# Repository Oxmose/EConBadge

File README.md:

# EConBadge
E-Ink Convention Badge | Connected badge to display your favorite images and texts at conventions.

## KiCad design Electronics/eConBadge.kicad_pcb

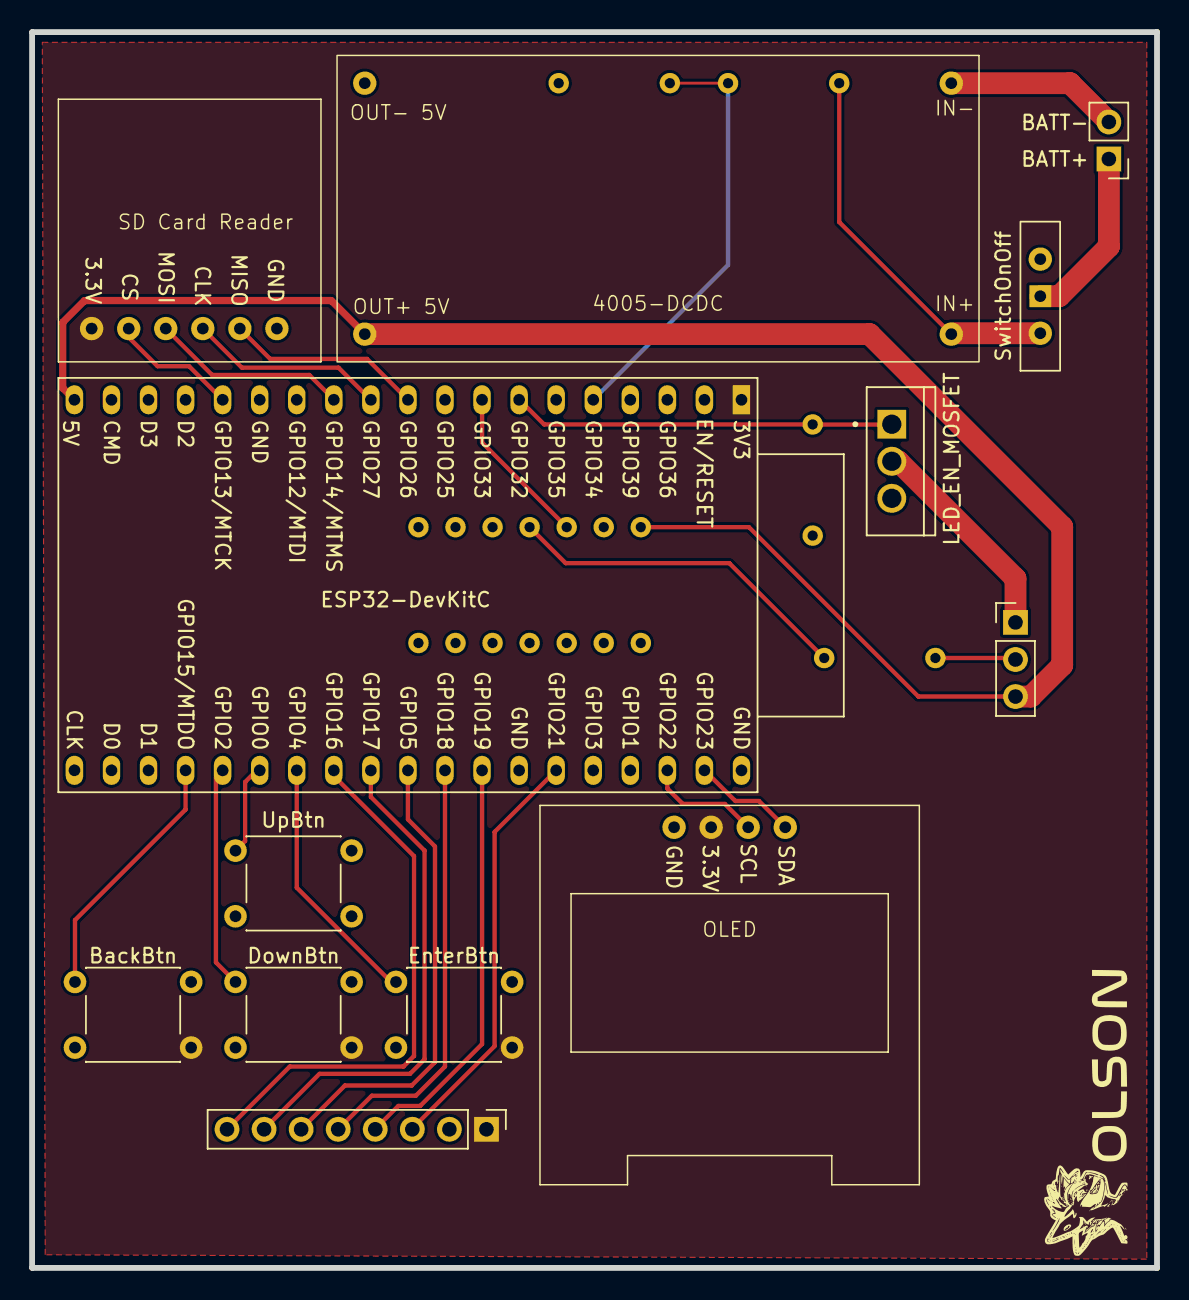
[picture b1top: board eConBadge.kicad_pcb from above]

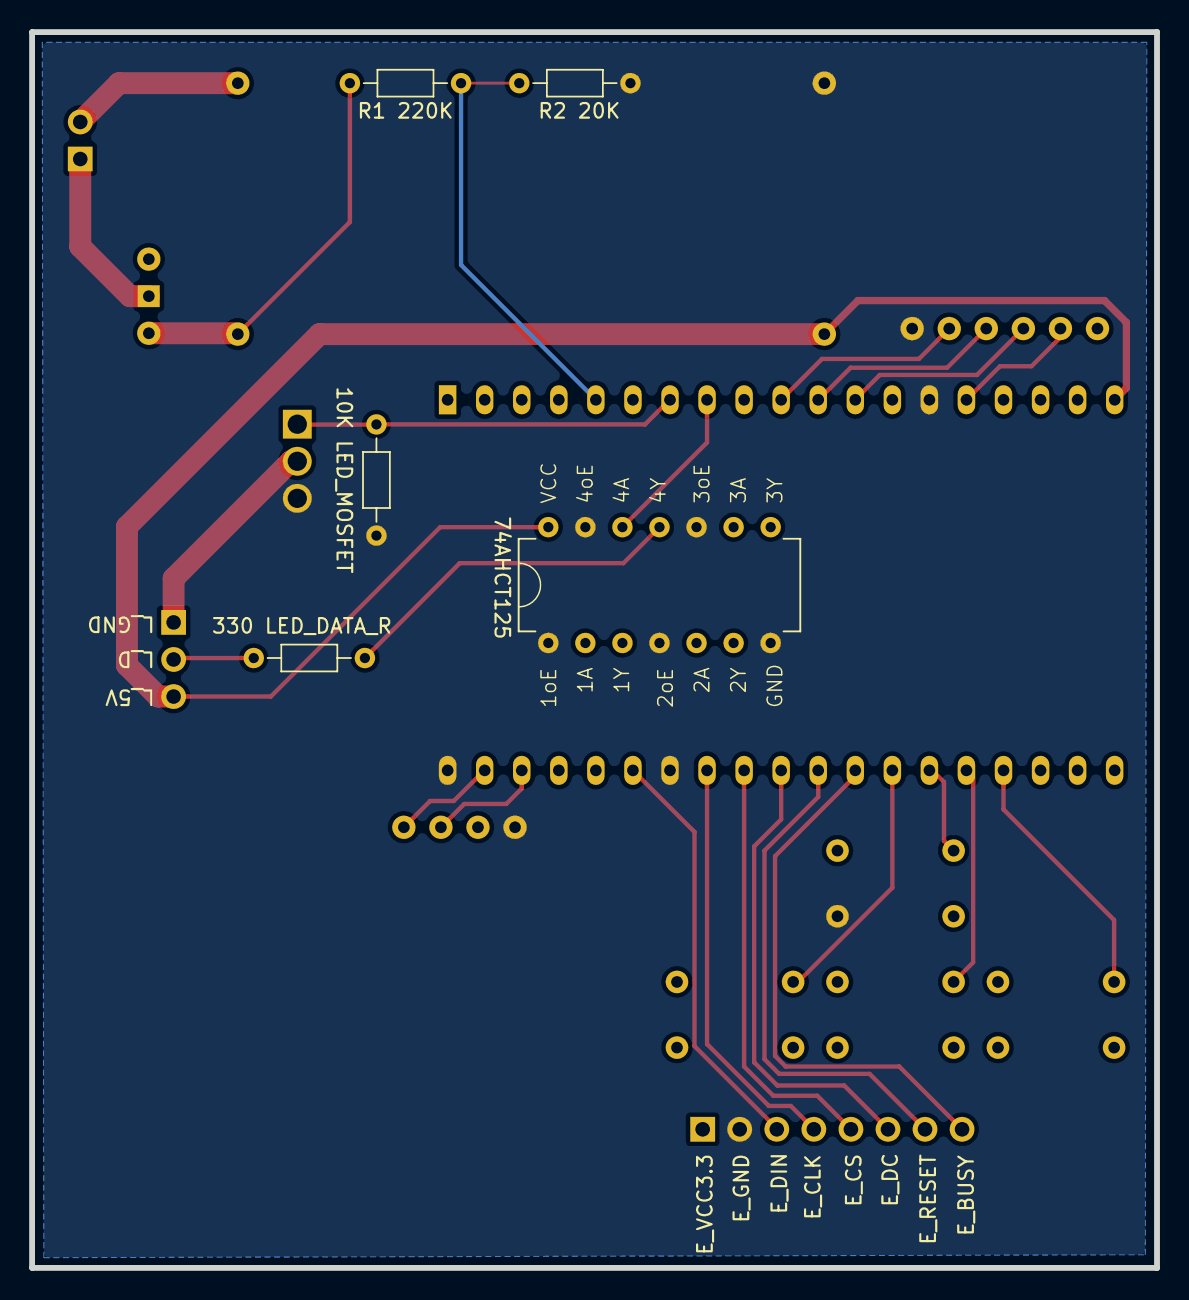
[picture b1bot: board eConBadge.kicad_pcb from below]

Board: 2 copper layers, 77.1 x 84.7 mm, 18 parts (5 on the bottom side), 28 nets.

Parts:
10K LED_MOSFET, 330 LED_DATA_R: R_Axial_DIN0204_L3.6mm_D1.6mm_P7.62mm_Horizontal
74AHCT125 : 74AHCT125; DIP794W45P254L1930H508Q14
4005-DCDC: DC-DC Regulator; 4005DCDC
BATT-: PinHeader_1x02_P2.54mm_Vertical
BackBtn: Button
DownBtn: Button
EInkConnector: PinHeader_1x08_P2.54mm_Vertical
ESP32: ESP32-DevKitC
EnterBtn: Button
LEDConnector: PinHeader_1x03_P2.54mm_Vertical
LED_EN_MOSFET: TRANS_RFP30N06LE
OLED: SSD1306_0.96_OLED
R1 220K: R_Axial_DIN0204_L3.6mm_D1.6mm_P7.62mm_Horizontal
R2 20K: R2 20K; R_Axial_DIN0204_L3.6mm_D1.6mm_P7.62mm_Horizontal
SDCardReader: 10k; SDCardReader
SwitchOnOff: SW_Slide-03_Wuerth-WS-SLTV_10x2.5x6.4_P2.54mm
UpBtn: Button

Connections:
BATT_IN_GND: 4005-DCDC.4, BATT-.2
BATT_IN_REG: 4005-DCDC.3, R1 220K.1, SwitchOnOff.2
BATT_IN_VCC: BATT-.1, SwitchOnOff.1
BATT_V_MEASURE: ESP32.5, R1 220K.2, R2 20K.1
BTN_BACK: BackBtn.1, ESP32.23
BTN_DOWN: DownBtn.1, ESP32.24
BTN_ENTER: ESP32.26, EnterBtn.1
BTN_UP: ESP32.25, UpBtn.1
EINK_BUSY: EInkConnector.8, ESP32.27
EINK_CLK: EInkConnector.4, ESP32.31
EINK_CS: EInkConnector.5, ESP32.30
EINK_DC: EInkConnector.6, ESP32.29
EINK_DIN: EInkConnector.3, ESP32.33
EINK_RESET: EInkConnector.7, ESP32.28
GND: 10K LED_MOSFET.1, 74AHCT125.1, 74AHCT125.4, 74AHCT125.7, 74AHCT125.10, 74AHCT125.13, 4005-DCDC.2, EInkConnector.2, ESP32.14, ESP32.32, ESP32.38, LED_EN_MOSFET.3, OLED.1, R2 20K.2, SDCardReader.6, UpBtn.2
LED_DATA_3V: 74AHCT125.12, ESP32.8
LED_DATA_5V_OUT: 330 LED_DATA_R.1, LEDConnector.2
LED_DATA_5V_SHIFT: 74AHCT125.11, 330 LED_DATA_R.2
LED_EN: 10K LED_MOSFET.2, ESP32.7, LED_EN_MOSFET.1
LED_GND: LEDConnector.1, LED_EN_MOSFET.2
OLED_CLK: ESP32.36, OLED.3
OLED_SDA: ESP32.37, OLED.4
SD_CLK: ESP32.11, SDCardReader.4
SD_CS: ESP32.15, SDCardReader.2
SD_MISO: ESP32.10, SDCardReader.5
SD_MOSI: ESP32.12, SDCardReader.3
VCC3.3: BackBtn.2, DownBtn.2, EInkConnector.1, ESP32.1, EnterBtn.2, OLED.2, SDCardReader.1
VCC_5V: 74AHCT125.14, 4005-DCDC.1, ESP32.19, LEDConnector.3

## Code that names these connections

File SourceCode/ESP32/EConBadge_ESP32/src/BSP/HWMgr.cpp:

/*******************************************************************************
 * @file HWMgr.cpp
 *
 * @author Alexy Torres Aurora Dugo
 *
 * @date 30/03/2021
 *
 * @version 1.0
 *
 * @brief This file defines the hardware layer.
 *
 * @details This file defines the hardware layer. This layer provides services
 * to interact with the ESP32 module hardware.
 *
 * @copyright Alexy Torres Aurora Dugo
 ******************************************************************************/


/*******************************************************************************
 * INCLUDES
 ******************************************************************************/
#include <string>      /* std::string*/
#include <Types.h>     /* Defined Types */
#include <Logger.h>    /* Logging service */
#include <esp_mac.h>   /* Mac address provider */
#include <esp_timer.h> /* Timer provider */

/* Header File */
#include <HWMgr.h>

/*******************************************************************************
 * CONSTANTS
 ******************************************************************************/
/* None */

/*******************************************************************************
 * MACROS
 ******************************************************************************/

/* None */

/*******************************************************************************
 * STRUCTURES AND TYPES
 ******************************************************************************/

/* None */

/*******************************************************************************
 * GLOBAL VARIABLES
 ******************************************************************************/

/************************* Imported global variables **************************/
/* None */

/************************* Exported global variables **************************/
/** @brief See HWManage.h */
std::string HWManager::HWUID_;
/** @brief See HWManage.h */
std::string HWManager::MACADDR_;
/** @brief See HWManage.h */
uint64_t HWManager::TIME_;

/** @brief Generic SPI bus */
SPIClass GEN_SPI(HSPI);

/************************** Static global variables ***************************/
/** @brief Decimal to Hexadecimal convertion table */
static const char spkHexTable[16] = {
    '0', '1', '2', '3', '4', '5', '6', '7',
    '8', '9', 'A', 'B', 'C', 'D', 'E', 'F'
};

/*******************************************************************************
 * STATIC FUNCTIONS DECLARATIONS
 ******************************************************************************/

/* None */

/*******************************************************************************
 * FUNCTIONS
 ******************************************************************************/

/* None */

/*******************************************************************************
 * CLASS METHODS
 ******************************************************************************/

const char* HWManager::GetHWUID(void)
{
    uint8_t value[6];
    uint8_t i;

    /* Check if the HWUID was already generated */
    if(HWUID_.size() == 0)
    {
        HWUID_ = "ECB-";

        esp_read_mac(value, ESP_MAC_BT);

        for(i = 0; i < 4; ++i)
        {
            HWUID_ += std::string(1, spkHexTable[(value[i] >> 4) & 0xF]) +
                      std::string(1, spkHexTable[value[i] & 0xF]);
        }
    }

    /* Copy HWUID */
    return HWUID_.c_str();
}

const char* HWManager::GetMacAddress(void)
{
    uint8_t i;
    uint8_t value[6];

    /* Check if the HWUID was already generated */
    if(MACADDR_.size() == 0)
    {
        esp_read_mac(value, ESP_MAC_BT);

        MACADDR_ = "";
        for(i = 0; i < 6; ++i)
        {
            MACADDR_ += std::string(1, spkHexTable[(value[i] >> 4) & 0xF]) +
                        std::string(1, spkHexTable[value[i] & 0xF]);
            if(i < 5)
            {
                MACADDR_ += ":";
            }
        }
    }

    /* Copy HWUID */
    return MACADDR_.c_str();
}

uint64_t HWManager::GetTime(void)
{
    TIME_ = (uint64_t)esp_timer_get_time();

    return TIME_;
}

void HWManager::Init(void)
{
    /* Begin ELINK and General SPI (with custom pins) */
    EINK_SPI.begin(GPIO_EINK_CLK, 33, GPIO_EINK_DIN, GPIO_EINK_CS);
    GENERAL_SPI.begin(GPIO_SD_CLK, GPIO_SD_MISO, GPIO_SD_MOSI, GPIO_SD_CS);

    /* Init time */
    TIME_ = 0;
}

void HWManager::DelayExecUs(const uint64_t kDelayUs)
{
    uint64_t passiveTime;
    uint64_t activeTime;
    uint64_t startTime;

    startTime = (uint64_t)esp_timer_get_time();

    /* Calculate how much we can spend in passive wait */
    passiveTime = kDelayUs / 1000 / portTICK_PERIOD_MS;

    /* Check if we can use a precise wait */
    if(passiveTime != 0)
    {
        vTaskDelay(passiveTime);
    }

    activeTime = (uint64_t)esp_timer_get_time() - startTime;

    /* Spend the rest for active time */
    if(activeTime < kDelayUs)
    {
        ets_delay_us(kDelayUs - activeTime);
    }
}

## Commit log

2022-12-16 Ajouté(e) GlobalSoftArchESP32
2022-12-16 Updated GlobalSoftArchESP32
2022-12-16 Added file structure and wiki links
2022-12-16 Mettre à jour GlobalSoftArchESP32
2022-12-17 First Draft GlobalSoftArchESP32
2022-12-17 Moved Design UML
2022-12-17 Added SCG version of diagram
2022-12-17 Added Wifi layer and command controler boilerplate
2022-12-18 Added IO management
2022-12-19 Added IO LED management, setup the control loop
2022-12-20 Debug mode is now an overlay mode
2022-12-20 Added menu management
2022-12-24 Updated the menu usage
2022-12-26 Added command management in wifi menu
2022-12-29 Added image management, eink display command and sleep modes
2023-01-03 Added pattern and animation management in LEDBorder
2023-01-03 Removed unwanted files
2023-01-21 Added LED border command management
2023-06-30 Restart project
2023-11-09 Rebooted project
2023-11-10 Added Bleutooth and Eink Driver and management
2023-11-10 Added LedBorder and BT response
2023-11-12 Finished LEDBorder implementation
2023-11-14 Image loading from SD card, revamped menu, Update OTA
2023-11-18 Started Android Application
2023-11-19 Added connection and dashboard to Android application
2023-12-03 Added led border management and started eink display management
2023-12-03 Udpated test
2023-12-09 Started cleaning code
2023-12-09 Cleaned code
2023-12-14 Cleaned code and added sleep mode
2023-12-14 Fixed LEDBorder init
2025-02-18 Reboot for clean code
2025-02-26 Updated to add updater
2025-03-07 Finished first beta ECB firmware, started Android app
2025-03-19 Added image management in android app Added PCB first prototype
    Also cleaned folder structure
2025-03-27 Started adding ledborder features to android app
2025-04-11 New PCB
2025-08-01 Save
